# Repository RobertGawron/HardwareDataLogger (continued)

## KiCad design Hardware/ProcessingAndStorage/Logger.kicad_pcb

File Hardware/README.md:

-5V    |  1  2  | 5V
    -3V3    |  3  4  | 3V3
    -12V    |  5  6  | 12V
     GND    |  7  8  | GND
   GPIO1    |  9 10  | GPIO2
   GPIO3    | 11 12  | GPIO4
   GPIO5    | 13 14  | GPIO6
   GPIO7    | 15 16  | GPIO8
   GPIO9    | 17 18  | GPIO10
  GPIO11    | 19 20  | GPIO12
 I2C_SCL    | 21 22  | I2C_SDA
     GND    | 23 24  | GND
 SPI_SCLK   | 25 26  | SPI_MOSI
 SPI_MISO   | 27 28  | SPI_CS1
 SPI_CS2    | 29 30  | SPI_CS3
     GND    | 31 32  | GND
 ANALOG1    | 33 34  | ANALOG2
 ANALOG3    | 35 36  | GND
 UART1_TX   | 37 38  | UART1_RX
 UART2_TX   | 39 40  | UART2_RX

 https://www.tme.eu/pl/details/zl212-40kg/listwy-i-gniazda-kolkowe/connfly/ds1022-2-20rf11/

 https://www.tme.eu/pl/details/ds1065-03-2x20s8bv/listwy-i-gniazda-kolkowe/connfly/ds1065-03-2-20s8bv/

 https://www.tme.eu/pl/details/stm32f103rbt6/mikrokontrolery-st/stmicroelectronics/

 kicad grid is 0.5 mmm

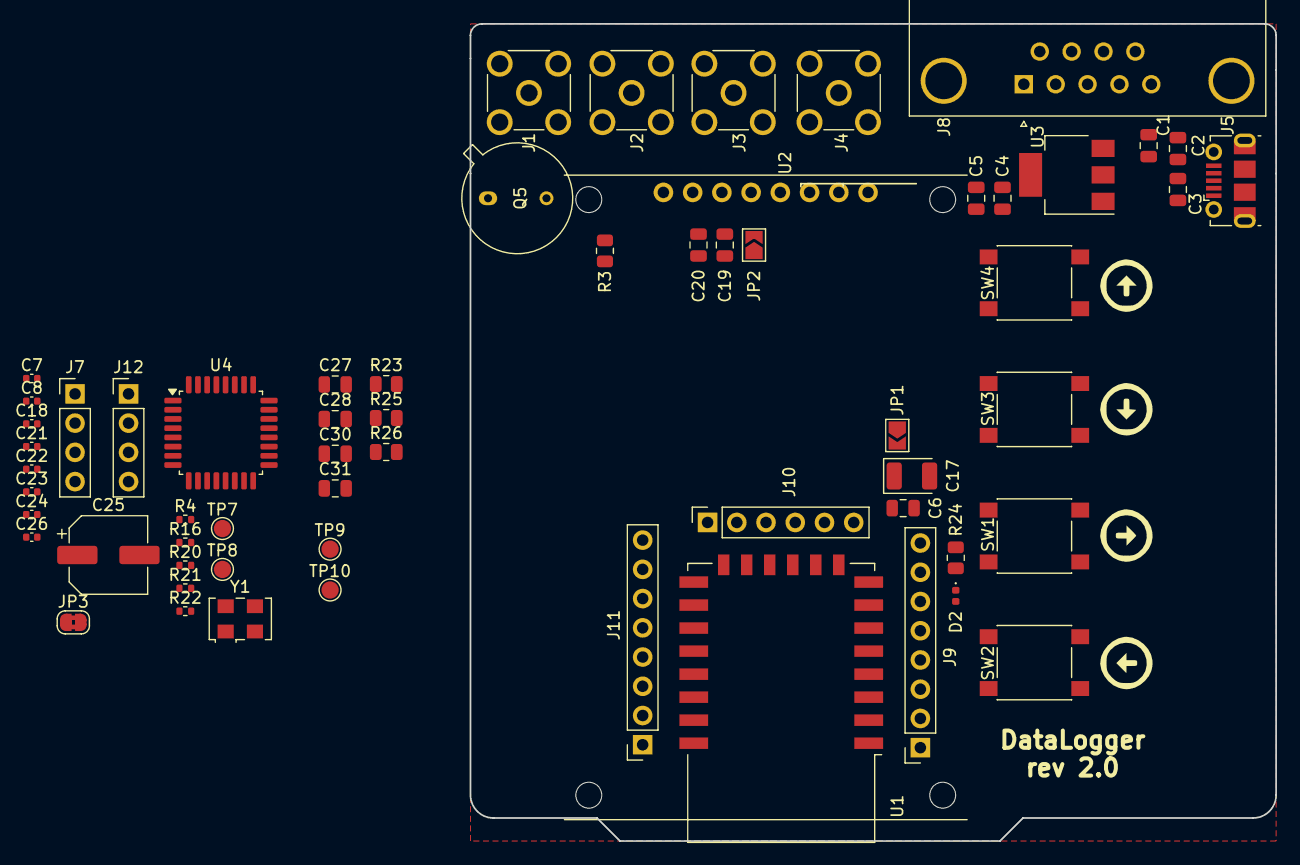
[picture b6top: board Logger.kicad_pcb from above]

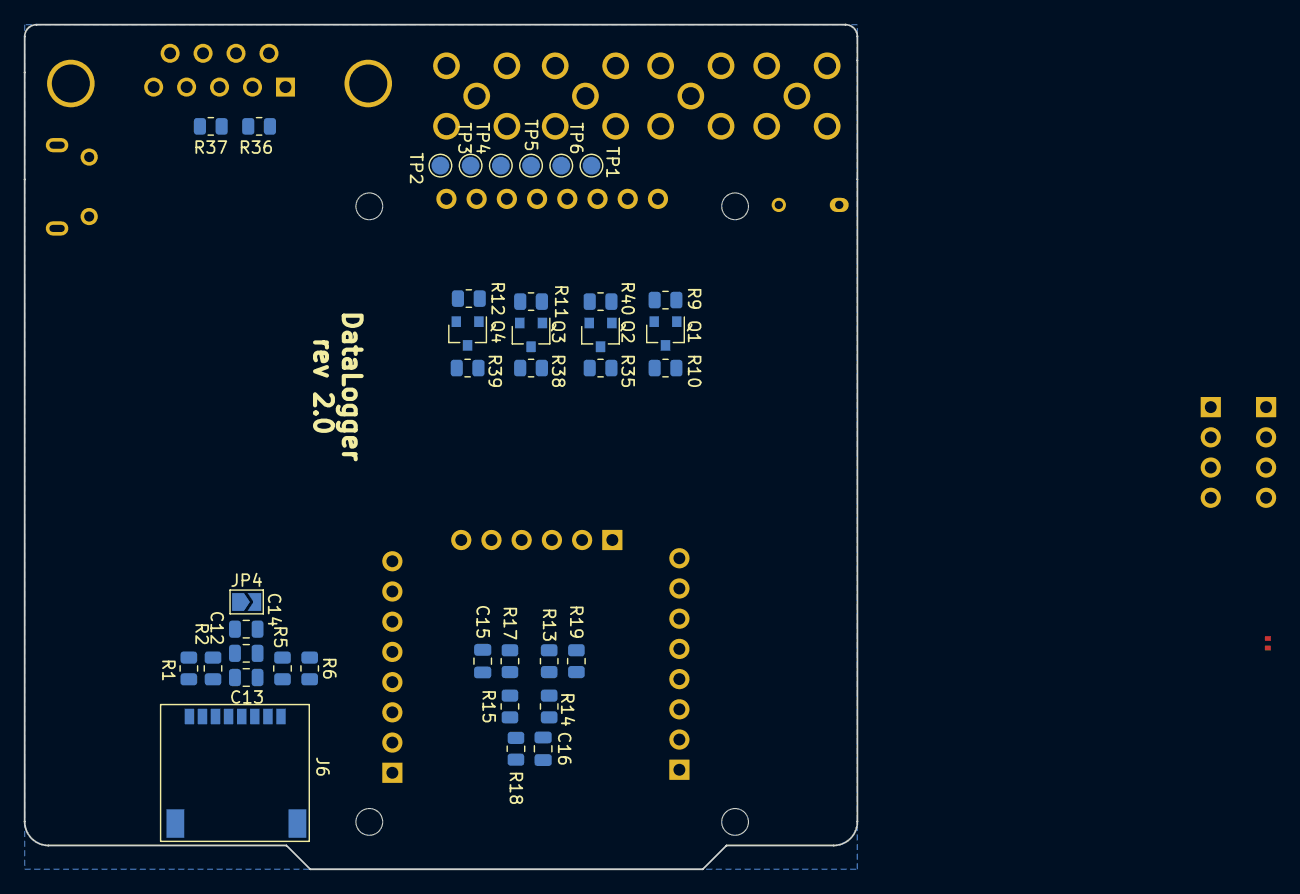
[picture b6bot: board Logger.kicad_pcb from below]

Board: 2 copper layers, 70.0 x 71.0 mm, 98 parts (37 on the bottom side), 65 nets, no tracks yet.

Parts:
C1, C2, C3, C4, C5, C12, C13, C14, C19, C20: 330n; C_0805_2012Metric
C6, C15: 100n; C_0805_2012Metric
C7, C8: 8p2; C_0402_1005Metric
C16: 470p; C_0805_2012Metric
C17: 47u/6V3; CP_EIA-3528-21_Kemet-B
C18, C21, C22, C23, C24, C26: 100n; C_0402_1005Metric
C25: 220u; CP_Elec_6.3x5.8
C27, C28, C30, C31: 3n3; C_0805_2012Metric
D2: LED; LED_0402_1005Metric
J1, J2, J3, J4: Conn_Coaxial; SMA_Molex_73251-2200_Horizontal
J5: USB_B_Micro; USB_Micro-B_Molex-105017-0001
J6: 112K-TAA0-RA1_ATTEND; 104B-TAA0-R_ATTEND
J7, J12: Conn_01x04_Female; PinHeader_1x04_P2.54mm_Vertical
J8: DE9_Plug_MountingHoles; DSUB-9_Female_Horizontal_P2.77x2.84mm_EdgePinOffset4.94mm_H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
J9, J11: Conn_01x08_Socket; PinSocket_1x08_P2.54mm_Vertical
J10: Conn_01x06_Socket; PinSocket_1x06_P2.54mm_Vertical
JP1, JP2, JP4: Jumper_2_Small_Open; SolderJumper-2_P1.3mm_Open_TrianglePad1.0x1.5mm
JP3: Jumper_NC_Small; SolderJumper-2_P1.3mm_Bridged2Bar_RoundedPad1.0x1.5mm
Q1, Q2, Q3, Q4: BC847A; SOT-23
Q5: Q_Photo_NPN; TO-5-2
R1, R2, R5, R6: 47R; R_0805_2012Metric
R3: 2M; R_0805_2012Metric
R4, R16: 2k2; R_0402_1005Metric
R9, R11, R12, R40: 1k; R_0805_2012Metric
R10, R35, R38, R39: 8k2; R_0805_2012Metric
R13, R14, R17, R18, R19: 10k; R_0805_2012Metric
R15, R23, R25, R26: 1k2; R_0805_2012Metric
R20: 10k; R_0402_1005Metric
R21, R22: 220R; R_0402_1005Metric
R24: 470R; R_0805_2012Metric
R36, R37: 100R; R_0805_2012Metric
SW1, SW2, SW3, SW4: SW_Push; SW_SPST_PTS645
TP1, TP2, TP3, TP4, TP5, TP6, TP7, TP8, TP9, TP10: TestPoint; TestPoint_Pad_D1.5mm
U1: ESP-12E
U2: ST7735S
U3: LD1117ASTR; SOT-223
U4: STM32F030K6Tx; LQFP-32_7x7mm_P0.8mm
Y1: 20MHz; Oscillator_SMD_EuroQuartz_XO53-4Pin_5.0x3.2mm

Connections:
3V3: C4.1, C5.1, JP1.1 (A), JP2.1 (A), JP4.1 (A), R3.1, R15.2, R23.2, R25.2, R26.2, U3.2 (OUT)
5V_DIGITAL: C18.1, C21.1, C22.1, C23.1, C24.1, C25.1, J12.4, R4.1, R16.1, R20.1, U4.1 (VDD), U4.5 (VDDA), U4.17 (VDD)
/DataProcessing/NRST: C26.1, J7.1, R20.2, U4.4 (NRST)
/DataProcessing/SWCLK: R22.1, U4.24 (PA14)
/DataProcessing/SWDIO: R21.1, U4.23 (PA13)
/DataProcessing/USART_RX: J12.3, U4.30 (PB7)
/DataProcessing/USART_TX: J12.2, U4.29 (PB6)
/WiFiInterface/EN: C15.1, J9.3, R17.2, U1.3 (EN)
/WiFiInterface/ESP32_CS0: J10.6, U1.9 (CS0)
/WiFiInterface/ESP32_MISO: J10.5, U1.10 (MISO)
/WiFiInterface/ESP32_MOSI: J10.2, U1.13 (MOSI)
/WiFiInterface/ESP32_SCLK: J10.1, U1.14 (SCLK)
/WiFiInterface/ESP_ADC: J9.2, U1.2 (ADC)
/WiFiInterface/GPIO2: J11.6, R13.2, U1.17 (GPIO2)
/WiFiInterface/GPIO4: J11.4, U1.19 (GPIO4)
/WiFiInterface/GPIO5: J11.3, U1.20 (GPIO5)
/WiFiInterface/GPIO9: J10.4, U1.11 (GPIO9)
/WiFiInterface/GPIO10: J10.3, U1.12 (GPIO10)
/WiFiInterface/GPIO12: J9.6, U1.6 (GPIO12)
/WiFiInterface/GPIO13: D2.2 (A), J9.7, U1.7 (GPIO13)
/WiFiInterface/GPIO14: J9.5, U1.5 (GPIO14)
/WiFiInterface/GPIO15: J11.7, R19.1, U1.16 (GPIO15)
/WiFiInterface/GPIO16: J9.4, U1.4 (GPIO16)
ANALOG_IN_1: Q1.3 (C), R25.1
ANALOG_IN_2: Q2.3 (C), R23.1
ANALOG_IN_3: Q3.3 (C), R15.1
ANALOG_IN_4: Q4.3 (C), R26.1
BACKGROUND_LIGHT_SENSOR: Q5.1 (C), R3.2
ESP32_FLASH_MODE: J11.5, R14.2, U1.18 (GPIO0)
ESP32_RST: C16.1, J9.1, R18.2, U1.1 (~RST)
ESP32_RX: J11.2, TP9.1, U1.21 (GPIO3/RXD)
ESP32_TX: J11.1, TP10.1, U1.22 (GPIO1/TXD)
ESP_PWR: C6.1, C17.1, J9.8, JP1.2 (B), R13.1, R14.1, R17.1, R18.1, U1.8 (VCC)
GND: C1.2, C2.2, C3.2, C4.2, C5.2, C6.2, C7.1, C8.1, C12.2, C13.2, C14.2, C15.2, C16.2, C17.2, C18.2, C19.2, C20.2, C21.2, C22.2, C23.2, C24.2, C25.2, C26.2, C27.2, C28.2, C30.2, C31.2, J1.2 (Ext), J2.2 (Ext), J3.2 (Ext), J4.2 (Ext), J5.5 (GND), J5.6 (Shield), J6.6 (VSS), J6.9 (SHELL1), J6.10 (SHELL2), J7.2, J11.8, J12.1, JP3.1, Q1.2 (E), Q2.2 (E), Q3.2 (E), Q4.2 (E), Q5.2 (E), R10.1, R19.2, R24.2, R35.1, R38.1, R39.1, SW1.1, SW2.1, SW3.1, SW4.1, U1.15 (GND), U2.1 (GND), U3.1 (ADJ), U4.16 (VSS), U4.32 (VSS), Y1.2, Y1.4
LCD_BRIGHT_PWM: TP2.1, U2.8 (BL)
unnamed: D2.1 (K), R24.1
unnamed: J1.1 (In), R9.1
unnamed: J2.1 (In), R40.1
unnamed: J3.1 (In), R11.1
unnamed: J4.1 (In), R12.1
unnamed: C1.1, C2.1, C3.1, J5.1 (VBUS), U3.3 (IN)
unnamed: J6.2 (CS), R1.2
unnamed: J6.3 (DI), R2.2
unnamed: J6.7 (DO), R6.2
unnamed: J6.5 (SCLK), R5.2
unnamed: C12.1, C13.1, C14.1, J6.4 (VDD), JP4.2 (B)
unnamed: J7.3, R22.2
unnamed: J7.4, R21.2
unnamed: J8.2, R36.2
unnamed: J8.3, R37.2
unnamed: C19.1, C20.1, JP2.2 (B), U2.2 (VCC)
unnamed: C27.1, Q1.1 (B), R9.2, R10.2
unnamed: C28.1, Q2.1 (B), R35.2, R40.2
unnamed: C30.1, Q3.1 (B), R11.2, R38.2
unnamed: C31.1, Q4.1 (B), R12.2, R39.2
unnamed: JP3.2, U4.31 (BOOT0)
unnamed: C7.2, U4.2 (PF0), Y1.3
unnamed: C8.2, U4.3 (PF1), Y1.1
SCL: R16.2, U4.19 (PA9)
SDA: R4.2, U4.20 (PA10)
SPI1_CS_LCD: TP3.1, U2.7 (CS)
SPI1_DC_LCD: TP4.1, U2.6 (DC)
SPI1_MOSI: R2.1, TP6.1, U2.4 (SDA), U4.13 (PA7)
SPI1_RST_LCD: TP5.1, U2.5 (RES)
SPI1_SCK: R5.1, TP1.1, U2.3 (SCL), U4.11 (PA5)

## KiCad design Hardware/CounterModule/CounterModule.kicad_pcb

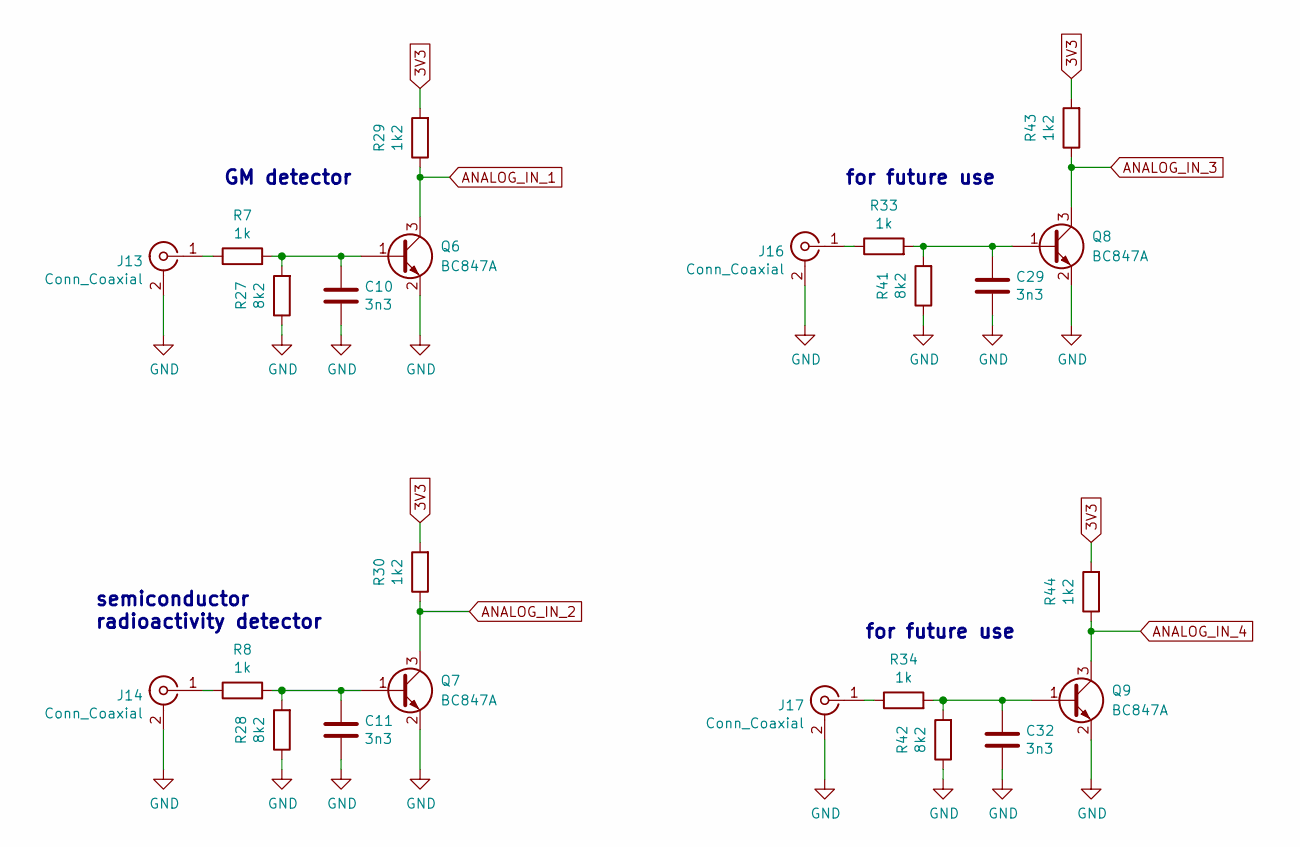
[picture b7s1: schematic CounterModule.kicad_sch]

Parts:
C10, C11, C29, C32: 3n3; C_0805_2012Metric
J13, J14, J16, J17: Conn_Coaxial; SMA_Molex_73251-2200_Horizontal
Q6, Q7, Q8, Q9: BC847A; SOT-23
R7, R8, R33, R34: 1k; R_0805_2012Metric
R27, R28, R41, R42: 8k2; R_0805_2012Metric
R29, R30, R43, R44: 1k2; R_0805_2012Metric

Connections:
3V3: R29.2, R30.2, R43.2, R44.2; also elsewhere on the board
ANALOG_IN_1: Q6.3 (C), R29.1
ANALOG_IN_2: Q7.3 (C), R30.1
ANALOG_IN_3: Q8.3 (C), R43.1
ANALOG_IN_4: Q9.3 (C), R44.1
GND: C10.2, C11.2, C29.2, C32.2, J13.2 (Ext), J14.2 (Ext), J16.2 (Ext), J17.2 (Ext), Q6.2 (E), Q7.2 (E), Q8.2 (E), Q9.2 (E), R27.1, R28.1, R41.1, R42.1
unnamed: J13.1 (In), R7.1
unnamed: J14.1 (In), R8.1
unnamed: J16.1 (In), R33.1
unnamed: J17.1 (In), R34.1
unnamed: C10.1, Q6.1 (B), R7.2, R27.2
unnamed: C11.1, Q7.1 (B), R8.2, R28.2
unnamed: C29.1, Q8.1 (B), R33.2, R41.2
unnamed: C32.1, Q9.1 (B), R34.2, R42.2

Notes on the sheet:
semiconductor radioactivity detector
GM detector
for future use

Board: 2 copper layers, 25 parts (1 on the bottom side), 14 nets, no tracks yet.

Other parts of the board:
JP4: Jumper_2_Small_Open; SolderJumper-2_P1.3mm_Open_TrianglePad1.0x1.5mm

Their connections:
3V3: JP4.1 (A); also elsewhere on the board

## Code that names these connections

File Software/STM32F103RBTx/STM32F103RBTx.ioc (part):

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Mcu.Name=STM32F103R(8-B)Tx
Mcu.Package=LQFP64
Mcu.UserName=STM32F103RBTx
PA10.Mode=Synchronous
PA10.Signal=USART1_RX
PA13.GPIOParameters=GPIO_Label
PA13.GPIO_Label=TMS
PA13.Mode=Serial_Wire
PA13.Signal=SYS_JTMS-SWDIO
PA14.GPIOParameters=GPIO_Label
PA14.GPIO_Label=TCK
PA14.Mode=Serial_Wire
PA14.Signal=SYS_JTCK-SWCLK
PA15.GPIOParameters=GPIO_Speed,PinState,GPIO_PuPd,GPIO_Label
PA15.GPIO_Label=LCD_DC
PA15.GPIO_PuPd=GPIO_NOPULL
PA15.GPIO_Speed=GPIO_SPEED_FREQ_HIGH
PA15.PinState=GPIO_PIN_RESET
PA15.Signal=GPIO_Output
PA2.GPIOParameters=GPIO_Speed,GPIO_PuPd,GPIO_Label,GPIO_Mode
PA2.GPIO_Label=USART_TX
PA2.GPIO_Mode=GPIO_MODE_AF_PP
PA2.GPIO_PuPd=GPIO_NOPULL
PA2.GPIO_Speed=GPIO_SPEED_FREQ_LOW
PA2.Mode=Synchronous
PA2.Signal=USART2_TX
PA3.GPIOParameters=GPIO_Speed,GPIO_PuPd,GPIO_Label,GPIO_Mode
PA3.GPIO_Label=USART_RX
PA3.GPIO_Mode=GPIO_MODE_AF_PP
PA3.GPIO_PuPd=GPIO_NOPULL
PA3.GPIO_Speed=GPIO_SPEED_FREQ_LOW
PA3.Mode=Synchronous
PA3.Signal=USART2_RX
PA4.Mode=Synchronous
PA4.Signal=USART2_CK
PA5.Mode=Full_Duplex_Master
PA5.Signal=SPI1_SCK
PA6.GPIOParameters=GPIO_PuPd,GPIO_Mode
PA6.GPIO_Mode=GPIO_MODE_INPUT
PA6.GPIO_PuPd=GPIO_PULLUP
PA6.Mode=Full_Duplex_Master
PA6.Signal=SPI1_MISO
PA7.Mode=Full_Duplex_Master
PA7.Signal=SPI1_MOSI
PA8.Mode=Synchronous
PA8.Signal=USART1_CK
PA9.Mode=Synchronous
PA9.Signal=USART1_TX
PB0.Signal=S_TIM3_CH3
PB1.Signal=S_TIM3_CH4
PB10.Mode=I2C
PB10.Signal=I2C2_SCL
PB11.Mode=I2C
PB11.Signal=I2C2_SDA
PB13.Mode=Full_Duplex_Master
PB13.Signal=SPI2_SCK
PB14.Mode=Full_Duplex_Master
PB14.Signal=SPI2_MISO
PB15.Mode=Full_Duplex_Master
PB15.Signal=SPI2_MOSI
PB2.GPIOParameters=PinState,GPIO_Label,GPIO_ModeDefaultOutputPP
PB2.GPIO_Label=LCD_RST
PB2.GPIO_ModeDefaultOutputPP=GPIO_MODE_OUTPUT_PP
PB2.PinState=GPIO_PIN_SET
PB2.Signal=GPIO_Output
PB3.GPIOParameters=GPIO_Label
PB3.GPIO_Label=SWO
PB3.Signal=SYS_JTDO-TRACESWO
PB4.GPIOParameters=GPIO_Speed,GPIO_PuPd,GPIO_Label
PB4.GPIO_Label=SD_CS
PB4.GPIO_PuPd=GPIO_PULLUP
PB4.GPIO_Speed=GPIO_SPEED_FREQ_HIGH
PB4.Signal=GPIO_Output
PB6.Mode=I2C
PB6.Signal=I2C1_SCL
PB7.Mode=I2C
PB7.Signal=I2C1_SDA
PB8.Mode=CAN_Activate
PB8.Signal=CAN_RX
PB9.Mode=CAN_Activate
PB9.Signal=CAN_TX
PC0.GPIOParameters=GPIO_PuPd,GPIO_Label
PC0.GPIO_Label=KEY_LEFT
PC0.GPIO_PuPd=GPIO_PULLUP
PC0.Signal=GPIO_Input
PC1.GPIOParameters=GPIO_PuPd,GPIO_Label
PC1.GPIO_Label=KEY_RIGHT
PC1.GPIO_PuPd=GPIO_PULLUP
PC1.Signal=GPIO_Input
PC10.Mode=Synchronous
PC10.Signal=USART3_TX
PC11.Mode=Synchronous
PC11.Signal=USART3_RX
PC12.Mode=Synchronous
PC12.Signal=USART3_CK
PC13-TAMPER-RTC.GPIOParameters=GPIO_Label
PC13-TAMPER-RTC.GPIO_Label=USB_ENUM
PC13-TAMPER-RTC.Signal=GPIO_Output
PC14-OSC32_IN.Mode=LSE-External-Oscillator
PC14-OSC32_IN.Signal=RCC_OSC32_IN
PC15-OSC32_OUT.Mode=LSE-External-Oscillator
PC15-OSC32_OUT.Signal=RCC_OSC32_OUT
PC2.GPIOParameters=GPIO_PuPd,GPIO_Label
PC2.GPIO_Label=KEY_UP
PC2.GPIO_PuPd=GPIO_PULLUP
PC2.Signal=GPIO_Input
PC3.GPIOParameters=GPIO_PuPd,GPIO_Label
PC3.GPIO_Label=KEY_DOWN
PC3.GPIO_PuPd=GPIO_PULLUP
PC3.Signal=GPIO_Input
PC4.Signal=ADCx_IN14
PC5.Signal=ADCx_IN15
PC6.Signal=GPXTI6
PC7.Signal=GPXTI7
PC8.Signal=GPXTI8
PC9.Signal=GPXTI9
PD0-OSC_IN.Mode=HSE-External-Oscillator
PD0-OSC_IN.Signal=RCC_OSC_IN
PD1-OSC_OUT.Mode=HSE-External-Oscillator
PD1-OSC_OUT.Signal=RCC_OSC_OUT
PD2.GPIOParameters=GPIO_Speed,PinState,GPIO_PuPd,GPIO_Label,GPIO_ModeDefaultOutputPP
PD2.GPIO_Label=LCD_CS
PD2.GPIO_ModeDefaultOutputPP=GPIO_MODE_OUTPUT_PP
PD2.GPIO_PuPd=GPIO_NOPULL
PD2.GPIO_Speed=GPIO_SPEED_FREQ_HIGH
PD2.PinState=GPIO_PIN_SET
PD2.Signal=GPIO_Output
RCC.SYSCLKFreq_VALUE=72000000
RCC.SYSCLKSource=RCC_SYSCLKSOURCE_PLLCLK
board=NUCLEO-F103RB
boardIOC=true

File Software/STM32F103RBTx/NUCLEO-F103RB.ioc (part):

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Mcu.Name=STM32F103R(8-B)Tx
Mcu.Package=LQFP64
Mcu.UserName=STM32F103RBTx
PA11.Mode=Device
PA11.Signal=USB_DM
PA12.Mode=Device
PA12.Signal=USB_DP
PA13.GPIOParameters=GPIO_Label
PA13.GPIO_Label=TMS
PA13.Mode=Serial_Wire
PA13.Signal=SYS_JTMS-SWDIO
PA14.GPIOParameters=GPIO_Label
PA14.GPIO_Label=TCK
PA14.Mode=Serial_Wire
PA14.Signal=SYS_JTCK-SWCLK
PA2.GPIOParameters=GPIO_Speed,GPIO_PuPd,GPIO_Label,GPIO_Mode
PA2.GPIO_Label=USART_TX
PA2.GPIO_Mode=GPIO_MODE_AF_PP
PA2.GPIO_PuPd=GPIO_NOPULL
PA2.GPIO_Speed=GPIO_SPEED_FREQ_LOW
PA2.Mode=Asynchronous
PA2.Signal=USART2_TX
PA3.GPIOParameters=GPIO_Speed,GPIO_PuPd,GPIO_Label,GPIO_Mode
PA3.GPIO_Label=USART_RX
PA3.GPIO_Mode=GPIO_MODE_AF_PP
PA3.GPIO_PuPd=GPIO_NOPULL
PA3.GPIO_Speed=GPIO_SPEED_FREQ_LOW
PA3.Mode=Asynchronous
PA3.Signal=USART2_RX
PA4.GPIOParameters=GPIO_PuPd,GPIO_Label
PA4.GPIO_Label=SD_CS
PA4.GPIO_PuPd=GPIO_PULLUP
PA4.Signal=GPIO_Output
PA5.Mode=Full_Duplex_Master
PA5.Signal=SPI1_SCK
PA6.GPIOParameters=GPIO_PuPd
PA6.GPIO_PuPd=GPIO_PULLUP
PA6.Mode=Full_Duplex_Master
PA6.Signal=SPI1_MISO
PA7.Mode=Full_Duplex_Master
PA7.Signal=SPI1_MOSI
PA8.GPIOParameters=GPIO_PuPd,GPIO_Label
PA8.GPIO_Label=SPI1_DC_LCD
PA8.GPIO_PuPd=GPIO_PULLUP
PA8.Signal=GPIO_Output
PB1.GPIOParameters=GPIO_PuPd,GPIO_Label
PB1.GPIO_Label=SPI1_CS_LCD
PB1.GPIO_PuPd=GPIO_PULLUP
PB1.Signal=GPIO_Output
PB3.GPIOParameters=GPIO_Label
PB3.GPIO_Label=SWO
PB3.Signal=SYS_JTDO-TRACESWO
PB5.GPIOParameters=GPIO_Speed,GPIO_Label
PB5.GPIO_Label=LCD_BACKLIGHT_PWM
PB5.GPIO_Speed=GPIO_SPEED_FREQ_HIGH
PB5.Signal=S_TIM3_CH2
PC0.GPIOParameters=GPIO_PuPd,GPIO_Label
PC0.GPIO_Label=KEY_LEFT
PC0.GPIO_PuPd=GPIO_PULLUP
PC0.Signal=GPIO_Input
PC1.GPIOParameters=GPIO_PuPd,GPIO_Label
PC1.GPIO_Label=KEY_RIGHT
PC1.GPIO_PuPd=GPIO_PULLUP
PC1.Signal=GPIO_Input
PC10.GPIOParameters=GPIO_Label
PC10.GPIO_Label=ESP32_TX
PC10.Mode=Asynchronous
PC10.Signal=USART3_TX
PC11.GPIOParameters=GPIO_Label
PC11.GPIO_Label=ESP32_RX
PC11.Mode=Asynchronous
PC11.Signal=USART3_RX
PC12.Signal=USART3_CK
PC13-TAMPER-RTC.GPIOParameters=GPIO_PuPd,GPIO_Label
PC13-TAMPER-RTC.GPIO_Label=B1 [Blue PushButton]
PC13-TAMPER-RTC.GPIO_PuPd=GPIO_NOPULL
PC13-TAMPER-RTC.Signal=GPXTI13
PC14-OSC32_IN.Mode=LSE-External-Oscillator
PC14-OSC32_IN.Signal=RCC_OSC32_IN
PC15-OSC32_OUT.Mode=LSE-External-Oscillator
PC15-OSC32_OUT.Signal=RCC_OSC32_OUT
PC2.GPIOParameters=GPIO_PuPd,GPIO_Label
PC2.GPIO_Label=KEY_UP
PC2.GPIO_PuPd=GPIO_PULLUP
PC2.Signal=GPIO_Input
PC3.GPIOParameters=GPIO_PuPd,GPIO_Label
PC3.GPIO_Label=KEY_DOWN
PC3.GPIO_PuPd=GPIO_PULLUP
PC3.Signal=GPIO_Input
PC4.GPIOParameters=GPIO_Label
PC4.GPIO_Label=BNC_4
PC4.Signal=GPXTI4
PC5.GPIOParameters=GPIO_Label
PC5.GPIO_Label=BACKGROUND_LIGHT_SENSOR
PC5.Signal=ADCx_IN15
PC6.GPIOParameters=PinState,GPIO_Label
PC6.GPIO_Label=ESP32_FLASH_MODE
PC6.PinState=GPIO_PIN_SET
PC6.Signal=GPIO_Output
PC7.GPIOParameters=PinState,GPIO_PuPd,GPIO_Label
PC7.GPIO_Label=SPI1_RST_LCD
PC7.GPIO_PuPd=GPIO_PULLUP
PC7.PinState=GPIO_PIN_SET
PC7.Signal=GPIO_Output
PC8.GPIOParameters=PinState,GPIO_Label
PC8.GPIO_Label=ESP32_RST
PC8.PinState=GPIO_PIN_SET
PC8.Signal=GPIO_Output
PD0-OSC_IN.Mode=HSE-External-Oscillator
PD0-OSC_IN.Signal=RCC_OSC_IN
PD1-OSC_OUT.Mode=HSE-External-Oscillator
PD1-OSC_OUT.Signal=RCC_OSC_OUT
RCC.SYSCLKFreq_VALUE=48000000
RCC.SYSCLKSource=RCC_SYSCLKSOURCE_PLLCLK
board=STM32F103RBTx
boardIOC=true

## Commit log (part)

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2020-10-15 add README.md
2020-10-15 Porting from https://github.com/RobertGawron/GeigerMullerCounter/
2020-10-15 add documentation
2020-10-15 fix urls for images
2020-10-15 fix project name
2020-10-15 add hw keyboard support for simulation
2020-10-16 - fix compilation error fter spliting lcd display into two files - add hw button implementation for target build
2020-10-16 add histogram view
2020-10-17 fix type of indexes to allow buffer bigger than 128 elements
2020-10-17 draft of histogram test
2020-10-17 fixes due to probems found during unit tests
2020-10-23 add unit test build for ci
2020-10-23 add static code analysis build for ci
2020-10-23 add static code analysis build for ci (c files)
2020-10-23 fixed formatting
2020-10-23 exclude external libs from repo programming language statistics
2020-10-24 fix c linter issues
2020-11-06 Fix grammar mistakes (found by Code Spell Checker add-on in VSCode). (fix #22)
2020-12-06 Create LICENSE
2021-07-14 draft of new hdraft of new hw
2021-07-25 fix #27, fix #30, fix #32
2021-07-25 fix #37
2021-07-25 fix #38
2021-07-31 switched to kicad6, finished circuit and component placement on pcb
2021-08-01 add on silkscreen icons to describe purpouse of buttons
2021-08-01 fix #41
2021-08-15 cleanup after transition to KiCad6
2021-08-15 improve docs
2021-08-24 vanilla configuration
2021-08-25 porting mngm of keyabord from old version of the project (designed only for GM counter)
2021-08-25 added st7735s, it compiles ok, but is neither used nor its callback are implemented; updated docs
2021-08-25 fix img url, add info that NUCLEO-F091RC firmware is obsolete
2021-08-25 Feature/rev 2 0 (#47)
    * vanilla configuration
    * porting mngm of keyabord from old version of the project (designed only
    for GM counter)
    * added st7735s, it compiles ok, but is neither used nor its callback are implemented; updated docs
    * fix img url, add info that NUCLEO-F091RC firmware is obsolete
2021-08-25 Feature/rev 2 0 (#47) (#48)
    * vanilla configuration
    * porting mngm of keyabord from old version of the project (designed only
    for GM counter)
    * added st7735s, it compiles ok, but is neither used nor its callback are implemented; updated docs
    * fix img url, add info that NUCLEO-F091RC firmware is obsolete
2021-08-26 1) LCD shows data but it's malformed; 2) fix #46
2021-08-27 1) LCD works ok now 2) fix #49 3) fix #50
2021-08-27 fixed SPI connections to SD card, added ESD protection for SD card
2021-08-30 add missing files and modifs
2021-08-30 add sdcard lib
2021-08-30 sd card works ok
2021-08-31 cosmetic changees in wires locations
2021-08-31 porting of data structures to hold meassurements
2021-09-02 PoC of esp32 support (setting esp32 to flashing mode))
2021-09-03 apply actual gpio connections to stm32 board, changed photoresistor to phototransistor
2021-09-05 draft of common interafce for all logger services (sdcard, wifi, uart, bluetooth), update doc (current img of the device), add -very crude- support for uncrustify code formatter, update cppcheck buil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
2021-09-05 clarify architecture
2021-09-05 fix #82
2021-09-06 update docs and add missing files
2021-09-06 fixed links
2021-09-06 fixed links (even more)
2021-09-07 draft of state diagrams, update of deploy diagram
2021-09-08 rework of state diagram, rework of storage class diagram, add draft of component diagrams
2021-09-09 tmp class diagram for hmi
2021-09-11 fix #98, fix #65, fix #85, fix #86, fix #89, fix #99
2021-09-11 fixed directory pathes
2021-09-12 cleanup after merge mistake
2021-09-12 usable version, still problems with lib excludes, cppcheck is broken in this subject
    adc without dma
2021-09-12 a bit more realistic pwm for backlight, also tried to glue all backlight parts and have an api to expose actual realation between pwm and brightness -it doesn't work, generally this commit is a pie o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
2021-09-12 trying to exclude 3rd party libs is a never ending story with this file
2021-09-13 rework of hmi class diagram
2021-09-13 add components to storage class diagram to help for future rework
2021-09-14 remove component diagram, add class diagram for measurement devices, rework of storage class diagram
2021-09-18 fix #112, fix #113, fix #114
2021-09-18 brute force way to exclude libs
2021-09-19 Squashed 'Software/NUCLEO-F103RB/Middlewares/Third_Party/uGFX/' content from commit 4261a1fb
    git-subtree-dir: Software/NUCLEO-F103RB/Middlewares/Third_Party/uGFX
    git-subtree-split: 4261a1fb0b5d88e1826a723a9f06221314f50797
2021-09-19 add uGFX sources
2021-09-19 remove unneded tests
2021-09-19 uGFX compiles ok, linking fail
2021-09-19 add uGFX config
2021-09-25 build ok
2021-09-25 fixed linker script location, removed obsolete implementation
2021-09-25 uGFX compilation and linking ok, added label widget, not tested on HW
2021-09-26 minor cleqnup for uGFX
2021-09-26 improve project structure
2021-09-26 automatically format code using uncrustify
2021-09-26 zithout osciloscope, sebuging SPI is pointless, there is something wrong with the driver and I dont know what, I brough back old implementation
2021-09-26 fix #122; add missing files; add basic simulation config for eclipse; add entry file for simulation build - simulation build has compilation errors
2021-09-26 change top layer from Application to BuisnessLogic
2021-09-26 rework of all docs
2024-08-16 this is what was send for pcb production
2024-08-18 draft of rev 3.0, cleanup of repo from not fully open source libs
2024-09-06 Firmware, test and simulation implementation, improvments for CI.
2024-09-29 cmake cleanup
2024-09-29 fix #148, fix #146, fix #151, fix #157
2024-09-29 drop nucleo board, use microcontroller directly
2024-10-06 draft of mainboard
2024-11-11 remove nucleo board and fix simulation compilation
2024-11-16 remove old lib
2024-11-16 Squashed 'Software/STM32F103RBTx/Middlewares/Third_Party/stm32-st7735/' content from commit 393aa0b
    git-subtree-dir: Software/STM32F103RBTx/Middlewares/Third_Party/stm32-st7735
    git-subtree-split: 393aa0b5bd1a58b884d4f0ae8c5b91dde864ff75
2024-11-16 fix #33
2024-11-17 pcb draft
2024-12-11 Squashed 'Software/STM32F103RBTx/Middlewares/Third_Party/u8g2/' content from commit 3e68b4375
    git-subtree-dir: Software/STM32F103RBTx/Middlewares/Third_Party/u8g2
    git-subtree-split: 3e68b43752de293c3a3ddf6186e9775a393f3310
2024-12-11 fix u8g2 submodule issue
2024-12-13 no neeed for mvc, use features from ui lib directly
2024-12-13 simulate key press
2024-12-13 analyse data flow
2024-12-13 draft
2024-12-14 fix ci and docs improve
2024-12-14 add test for display content
2024-12-16 configure CodeChecker, fix part of issues found in code
2024-12-17 fix more errors find in static analysis
2024-12-17 add dev and ut for measurement data handling
2024-12-18 improve simulation gui and add its uml diagrams
2024-12-18 simulation can show input pulse counter values
2024-12-18 measurement storages integrated with hmi and simulation
2024-12-19 cleanup
2024-12-19 get rid of unsafe array from uart driver
2024-12-19 fix more arrays
2024-12-19 fixing mui wrapper
2024-12-19 fixing mui wrapper, success
2024-12-19 split to separate files
2024-12-19 add files
2024-12-19 add meassurement source
2024-12-19 mui cleanup
2024-12-19 fix get last meassurement
2024-12-19 fix DisplayBrightnessRegulator
2024-12-19 mui mem fix
2024-12-19 small
2024-12-19 semi populate id
2024-12-19 code cleanup
2024-12-20 graphana test
2024-12-20 docs cleanup
2024-12-21 initial draft
2024-12-21 python lint
2024-12-22 add python static analysis for ci
2024-12-22 esp init version
2024-12-22 fix ci
2024-12-27 draft of esp simu
2024-12-28 fix ci, only esp firmwre static analysis fails because it is work in progress
2024-12-28 draft of uart communication between stm32 and esp
2024-12-29 vanilla config
2024-12-31 cmake rework to avoid crash on firmware startup and draft of uart data link
2025-01-04 add common folder for packet decomutation
2025-06-28 sending pcb to fabirication
2025-09-27 corections after hw sw integration
2025-09-27 make boards smaller, fix sd card slot
2025-12-19 remove platform io
2025-12-21 make hw
2025-12-21 compile
2025-12-21 saturday
2025-12-24 test
2025-12-24 unify
2025-12-24 fix integration tests
2025-12-24 Fix formatting issues in README.md
2025-12-24 package
2025-12-24 add more ut
2025-12-24 fix cmake
2025-12-25 cleanup ci
2025-12-25 cleanup ci - 2025-12-25T10:08:18+01:00
2025-12-25 cleanup ci - 2025-12-25T10:13:07+01:00
2025-12-25 cleanup ci - 2025-12-25T10:14:09+01:00
2025-12-25 cleanup ci - 2025-12-25T10:20:25+01:00
2025-12-25 cleanup ci - 2025-12-25T10:21:04+01:00
2025-12-25 cleanup ci - 2025-12-25T10:25:11+01:00
2025-12-25 fixes
2025-12-25 ubdate ci
2025-12-25 oooooooooooooooooooxxx
2025-12-25 rework CI, make PCB smaller
2025-12-25 fix drv issues
2025-12-25 check
2025-12-26 drv cleanup
2025-12-26 dev cleanup
2025-12-27 paraller
2025-12-27 fix fw
2025-12-27 fw in main
2025-12-27 fw stat
2025-12-28 ci actions on main
2025-12-28 py static
2025-12-28 ling
2025-12-31 hw 4.1 pcb, ci rework
2025-12-31 ninja for build, improve README and integration tests
2026-01-01 fix ut, improve simulation
2026-01-01 python lint ok
2026-01-01 fix firmware startup crash
2026-01-01 p build
2026-01-01 fix cpp lint ci job
2026-01-01 modif mxcube tim2 tick
2026-01-01 impl
2026-01-03 c++23 transition
2026-01-04 remove vtable usage
2026-01-10 use cpp+20 module
2026-01-10 simu rewok wip
2026-01-11 in docker 1
2026-01-11 vs code
2026-01-11 ci fixes for firmware
2026-01-11 docs cov fix
2026-01-11 py cov fix
2026-01-11 more simu
2026-01-12 it compiles
2026-01-15 simulation rewok
2026-01-15 enviroment for flashing in docker
2026-01-15 tim2 to tick the app
2026-01-19 update elements values, add docs
2026-01-20 fix simulation build
2026-01-22 sd card code cleanup, poc ut with cpp+20 modules
2026-01-22 display and brightness drivers rework
2026-01-23 ambient driver fix
2026-01-23 counter wip
2026-01-23 pulse counter before hw integ
2026-01-23 fix kicad
2026-01-24 add shceduler
2026-01-24 add shceduler vip
2026-01-25 drv component impl wip
2026-01-25 key component impl wip
2026-01-25 fix keyboard
2026-06-28 hw 4.1 integration
2026-06-28 get rid of .h file
2026-06-28 finally works
2026-06-28 sim starts, init fails
